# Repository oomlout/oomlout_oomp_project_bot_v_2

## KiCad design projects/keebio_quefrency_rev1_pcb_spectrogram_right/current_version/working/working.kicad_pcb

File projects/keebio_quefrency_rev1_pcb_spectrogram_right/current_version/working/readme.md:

# quefrency_rev1_pcb
 
## summary 
* id: keebio_quefrency_rev1_pcb_spectrogram_right
* user: keebio
* name: quefrency_rev1_pcb
* board: spectrogram_right
* repo: https://github.com/keebio/quefrency-rev1-pcb
* src_file_repo_kicad_pcb: spectrogram-right/spectrogram-right.kicad_pcb
* src_file_repo_kicad_pcb_link: https://github.com/keebio/quefrency-rev1-pcb/tree/main/spectrogram-right/spectrogram-right.kicad_pcb
* src_file_repo_kicad_sch: quefrency-right-65/quefrency-right-65.kicad_sch
* src_file_repo_kicad_sch_link: https://github.com/keebio/quefrency-rev1-pcb/tree/main/quefrency-right-65/quefrency-right-65.kicad_sch

* src_file_repo_sch: spectrogram-right/spectrogram-right.sch
* src_file_repo_sch_link: https://github.com/keebio/quefrency-rev1-pcb/tree/main/spectrogram-right/spectrogram-right.sch
* full details link: https://github.com/oomlout/oomlout_oomp_project_bot_v_2/tree/main/projects/keebio_quefrency_rev1_pcb_spectrogram_right/current_version/working

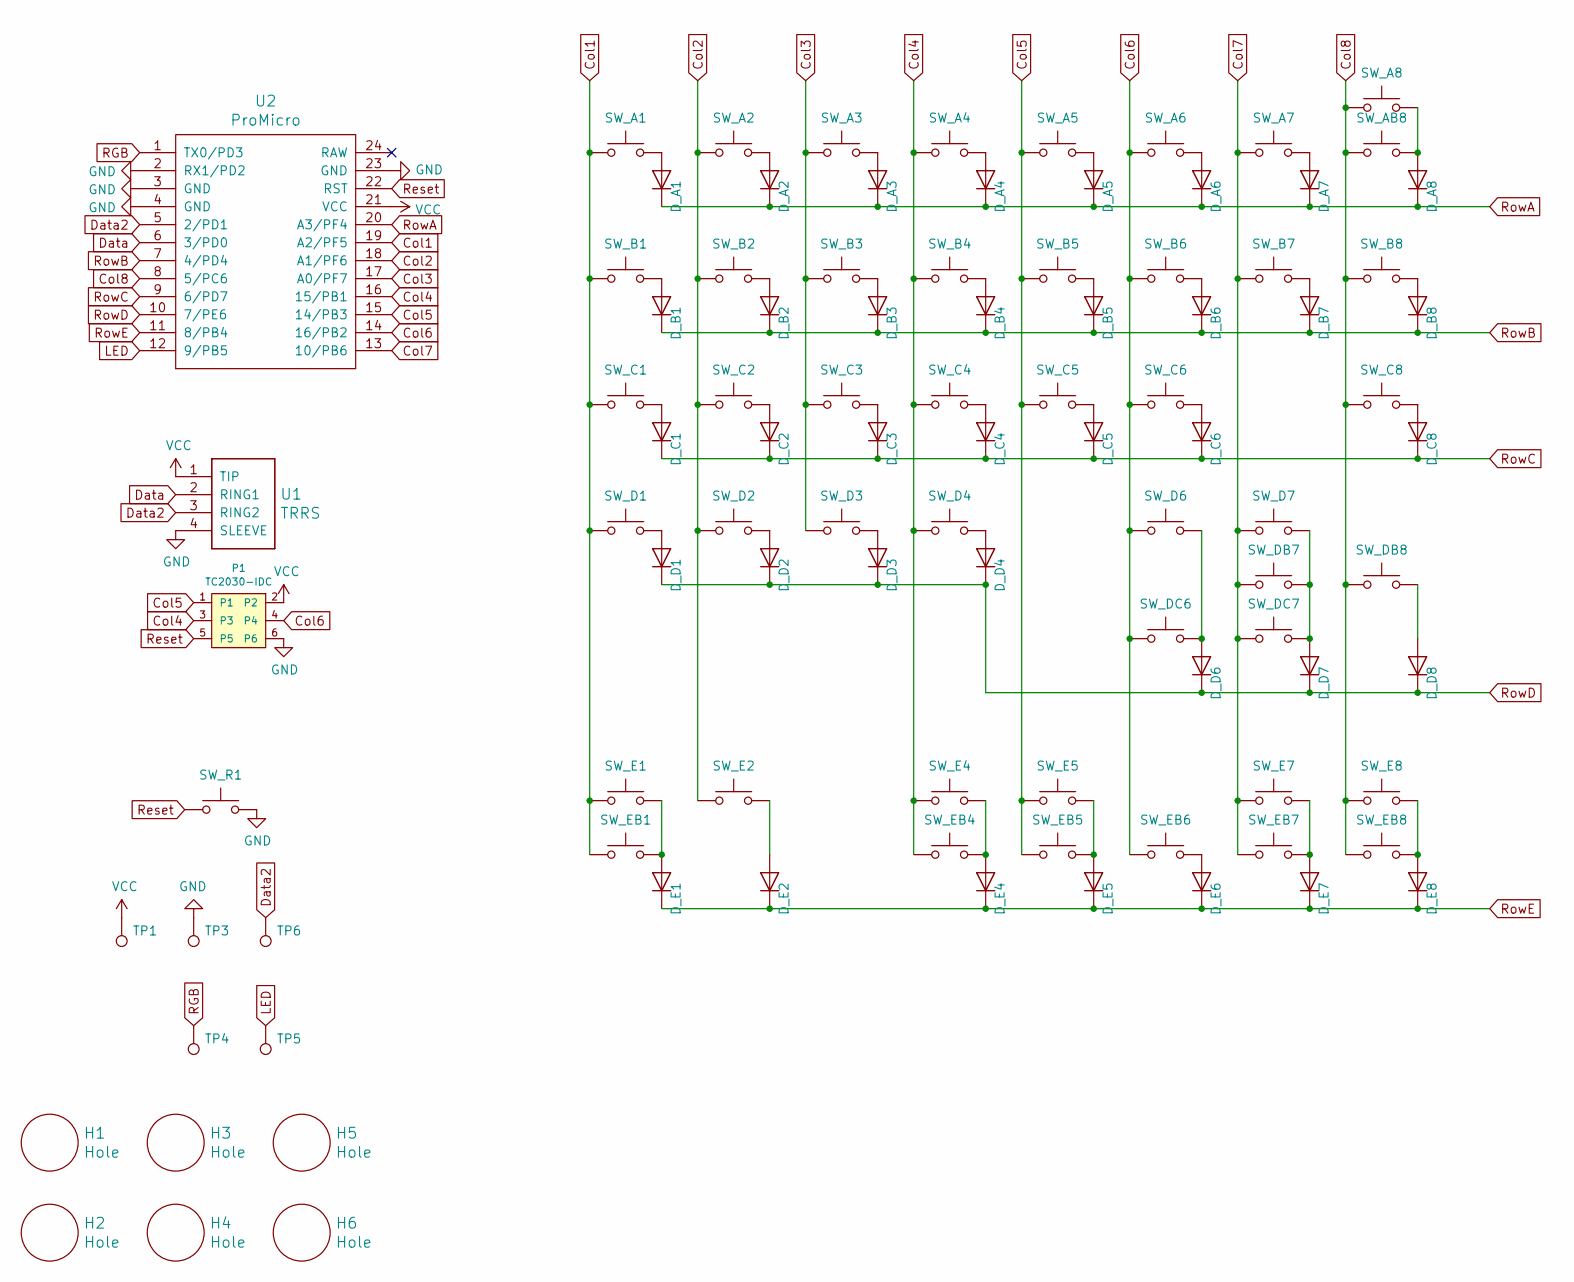
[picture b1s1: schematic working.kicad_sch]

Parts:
D_A1, D_A2, D_A3, D_A4, D_A5, D_A6, D_A7, D_A8: D; Diode-Hybrid-Back
D_B1, D_B2, D_B3, D_B4, D_B5, D_B6, D_B7, D_B8: D; Diode-Hybrid-Back
D_C1, D_C2, D_C3, D_C4, D_C5, D_C6, D_C8: D; Diode-Hybrid-Back
D_D1, D_D2, D_D3, D_D4, D_D6, D_D7, D_D8: D; Diode-Hybrid-Back
D_E1, D_E2, D_E4, D_E5, D_E6, D_E7, D_E8: D; Diode-Hybrid-Back
H1, H2, H3, H4, H5, H6: Hole; MountingHole_3.2mm_M3_ISO14580_Pad
P1: TC2030-IDC; TC2030-NL_SMALL
SW_A1, SW_A2, SW_A3, SW_A4, SW_A5, SW_A6, SW_A7: SW_Push; MX-1U-NoLED
SW_A8: SW_Push; MX-2U-ReversedStabilizers-NoLED
SW_AB8: SW_Push; MX-1U-NoLED
SW_B1, SW_B2, SW_B3, SW_B4, SW_B5, SW_B6, SW_B7: SW_Push; MX-1U-NoLED
SW_B8: SW_Push; MX-1.5U-NoLED
SW_C1, SW_C2, SW_C3, SW_C4, SW_C5, SW_C6: SW_Push; MX-1U-NoLED
SW_C8: SW_Push; MX-2.25U-NoLED
SW_D1, SW_D2, SW_D3, SW_D4, SW_D6: SW_Push; MX-1U-NoLED
SW_D7: SW_Push; MX-2.75U-NoLED
SW_DB7: SW_Push; MX-1.75U-NoLED
SW_DB8: SW_Push; MX-1U-NoLED
SW_DC6: SW_Push; MX-1.75U-NoLED
SW_DC7: SW_Push; MX-1U-NoLED
SW_E1: SW_Push; MX-2.75U-ReversedStabilizers-NoLED
SW_E2: SW_Push; MX-1.5U-NoLED
SW_E4, SW_E5, SW_E7, SW_E8: SW_Push; MX-1.25U-NoLED
SW_EB1: SW_Push; MX-1.25U-NoLED
SW_EB4, SW_EB5, SW_EB6, SW_EB7, SW_EB8: SW_Push; MX-1U-NoLED
SW_R1: Reset; SW_Tactile_SPST_Angled_MJTP1117
TP1: VCC; SinglePad
TP3: GND; SinglePad
TP4: RGB; SinglePad
TP5: LED; SinglePad
TP6: Extra Data; SinglePad
U1: TRRS; TRRS-PJ-320A
U2: ProMicro; ArduinoProMicro-ZigZag

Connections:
Col1: SW_A1.1, SW_B1.1, SW_C1.1, SW_D1.1, SW_E1.1, SW_EB1.1, U2.19 (A2/PF5)
Col2: SW_A2.1, SW_B2.1, SW_C2.1, SW_D2.1, SW_E2.1, U2.18 (A1/PF6)
Col3: SW_A3.1, SW_B3.1, SW_C3.1, SW_D3.1, U2.17 (A0/PF7)
Col4: P1.3, SW_A4.1, SW_B4.1, SW_C4.1, SW_D4.1, SW_E4.1, SW_EB4.1, U2.16 (15/PB1)
Col5: P1.1, SW_A5.1, SW_B5.1, SW_C5.1, SW_E5.1, SW_EB5.2, U2.15 (14/PB3)
Col6: P1.4, SW_A6.1, SW_B6.1, SW_C6.1, SW_D6.1, SW_DC6.2, SW_EB6.1, U2.14 (16/PB2)
Col7: SW_A7.1, SW_B7.1, SW_D7.2, SW_DB7.1, SW_DC7.2, SW_E7.1, SW_EB7.2, U2.13 (10/PB6)
Col8: SW_A8.1, SW_AB8.1, SW_B8.1, SW_C8.1, SW_DB8.1, SW_E8.1, SW_EB8.1, U2.8 (5/PC6)
Data: U1.2 (RING1), U2.6 (3/PD0)
Data2: TP6.1, U1.3 (RING2), U2.5 (2/PD1)
GND: P1.6, SW_R1.2, TP3.1, U1.4 (SLEEVE), U2.2 (RX1/PD2), U2.3 (GND), U2.4 (GND), U2.23 (GND)
LED: TP5.1, U2.12 (9/PB5)
unnamed: D_A1.2 (A), SW_A1.2
unnamed: D_A2.2 (A), SW_A2.2
unnamed: D_A3.2 (A), SW_A3.2
unnamed: D_A4.2 (A), SW_A4.2
unnamed: D_A5.2 (A), SW_A5.2
unnamed: D_A6.2 (A), SW_A6.2
unnamed: D_A7.2 (A), SW_A7.2
unnamed: D_A8.2 (A), SW_A8.2, SW_AB8.2
unnamed: D_B1.2 (A), SW_B1.2
unnamed: D_B2.2 (A), SW_B2.2
unnamed: D_B3.2 (A), SW_B3.2
unnamed: D_B4.2 (A), SW_B4.2
unnamed: D_B5.2 (A), SW_B5.2
unnamed: D_B6.2 (A), SW_B6.2
unnamed: D_B7.2 (A), SW_B7.2
unnamed: D_B8.2 (A), SW_B8.2
unnamed: D_C1.2 (A), SW_C1.2
unnamed: D_C2.2 (A), SW_C2.2
unnamed: D_C3.2 (A), SW_C3.2
unnamed: D_C4.2 (A), SW_C4.2
unnamed: D_C5.2 (A), SW_C5.2
unnamed: D_C6.2 (A), SW_C6.2
unnamed: D_C8.2 (A), SW_C8.2
unnamed: D_D1.2 (A), SW_D1.2
unnamed: D_D2.2 (A), SW_D2.2
unnamed: D_D3.2 (A), SW_D3.2
unnamed: D_D4.2 (A), SW_D4.2
unnamed: D_D6.2 (A), SW_D6.2, SW_DC6.1
unnamed: D_D7.2 (A), SW_D7.1, SW_DB7.2, SW_DC7.1
unnamed: D_D8.2 (A), SW_DB8.2
unnamed: D_E1.2 (A), SW_E1.2, SW_EB1.2
unnamed: D_E2.2 (A), SW_E2.2
unnamed: D_E4.2 (A), SW_E4.2, SW_EB4.2
unnamed: D_E5.2 (A), SW_E5.2, SW_EB5.1
unnamed: D_E6.2 (A), SW_EB6.2
unnamed: D_E7.2 (A), SW_E7.2, SW_EB7.1
unnamed: D_E8.2 (A), SW_E8.2, SW_EB8.2
RGB: TP4.1, U2.1 (TX0/PD3)
Reset: P1.5, SW_R1.1, U2.22 (RST)
RowA: D_A1.1 (K), D_A2.1 (K), D_A3.1 (K), D_A4.1 (K), D_A5.1 (K), D_A6.1 (K), D_A7.1 (K), D_A8.1 (K), U2.20 (A3/PF4)
RowB: D_B1.1 (K), D_B2.1 (K), D_B3.1 (K), D_B4.1 (K), D_B5.1 (K), D_B6.1 (K), D_B7.1 (K), D_B8.1 (K), U2.7 (4/PD4)
RowC: D_C1.1 (K), D_C2.1 (K), D_C3.1 (K), D_C4.1 (K), D_C5.1 (K), D_C6.1 (K), D_C8.1 (K), U2.9 (6/PD7)
RowD: D_D1.1 (K), D_D2.1 (K), D_D3.1 (K), D_D4.1 (K), D_D6.1 (K), D_D7.1 (K), D_D8.1 (K), U2.10 (7/PE6)
RowE: D_E1.1 (K), D_E2.1 (K), D_E4.1 (K), D_E5.1 (K), D_E6.1 (K), D_E7.1 (K), D_E8.1 (K), U2.11 (8/PB4)
VCC: P1.2, TP1.1, U1.1 (TIP), U2.21 (VCC)

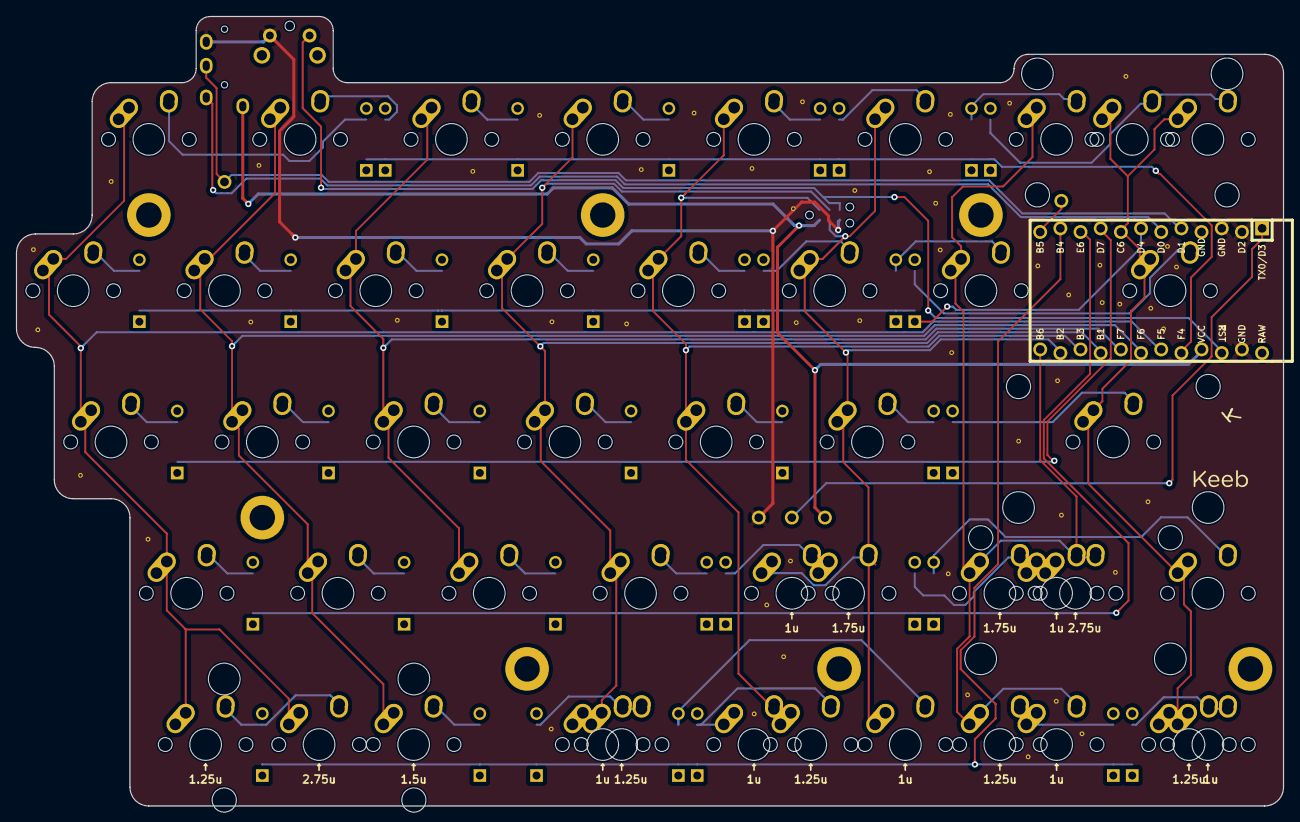
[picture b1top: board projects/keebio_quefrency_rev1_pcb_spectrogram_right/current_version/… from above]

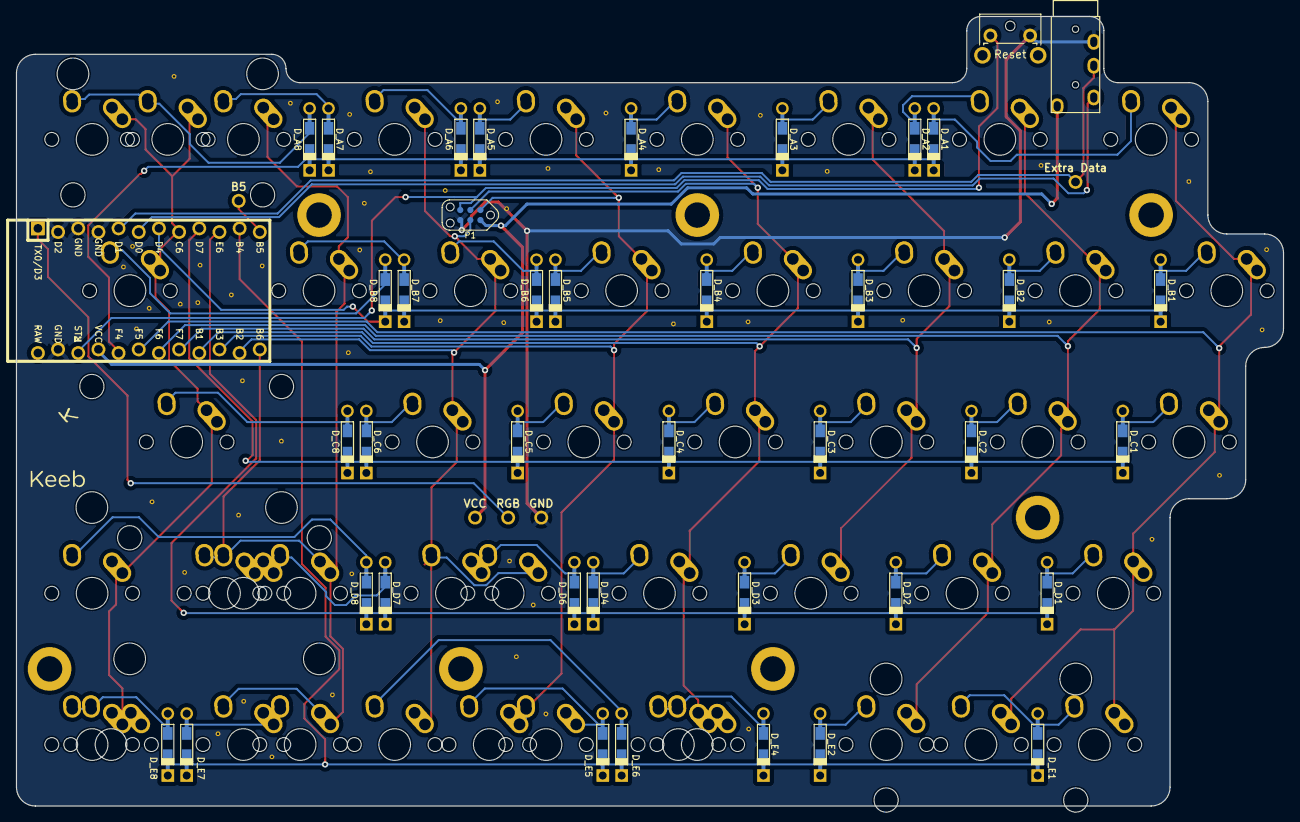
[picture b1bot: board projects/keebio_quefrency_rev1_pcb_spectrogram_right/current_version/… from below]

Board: 2 copper layers, 159.5 x 99.4 mm, 99 parts (8 on the bottom side), 57 nets.

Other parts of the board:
H6#2: Hole; MountingHole_3.2mm_M3_ISO14580_Pad

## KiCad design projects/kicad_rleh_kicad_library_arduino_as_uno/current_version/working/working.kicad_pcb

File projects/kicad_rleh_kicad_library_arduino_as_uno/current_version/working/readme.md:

# kicad_library
 
## summary 
* id: kicad_rleh_kicad_library_arduino_as_uno
* user: kicad_rleh
* name: kicad_library
* board: arduino_as_uno
* repo: https://github.com/kicad-rleh/kicad-library
* src_file_repo_kicad_pcb: template/Arduino_As_Uno_R3/Arduino_As_Uno.kicad_pcb
* src_file_repo_kicad_pcb_link: https://github.com/kicad-rleh/kicad-library/tree/master/template/Arduino_As_Uno_R3/Arduino_As_Uno.kicad_pcb

* src_file_repo_sch: template/Arduino_As_Uno_R3/Arduino_As_Uno.sch
* src_file_repo_sch_link: https://github.com/kicad-rleh/kicad-library/tree/master/template/Arduino_As_Uno_R3/Arduino_As_Uno.sch
* full details link: https://github.com/oomlout/oomlout_oomp_project_bot_v_2/tree/main/projects/kicad_rleh_kicad_library_arduino_as_uno/current_version/working

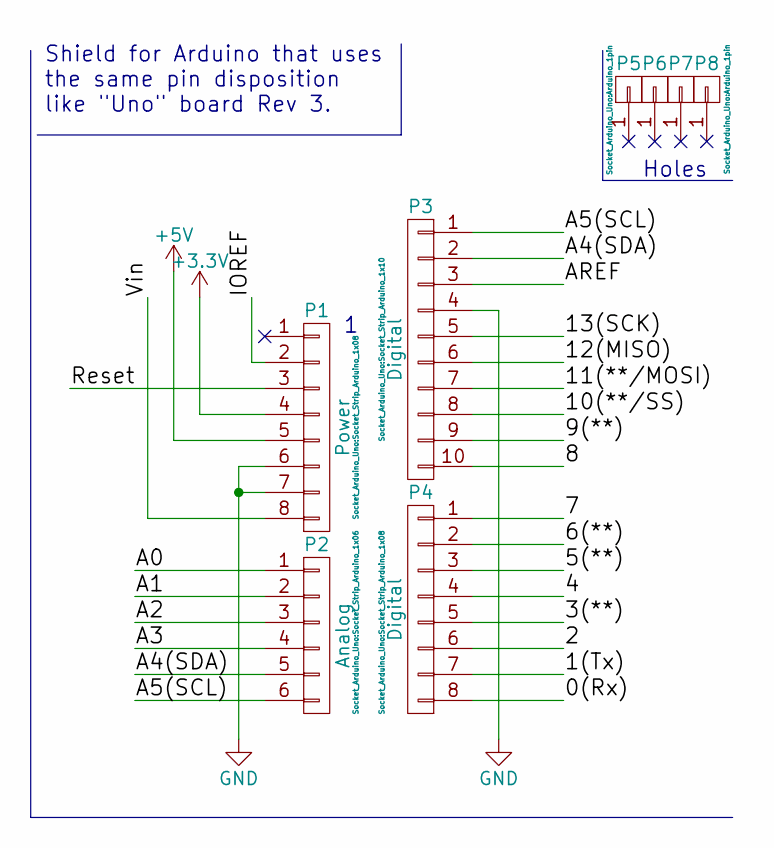
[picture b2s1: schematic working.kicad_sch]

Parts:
P1: Power; Socket_Strip_Arduino_1x08
P2: Analog; Socket_Strip_Arduino_1x06
P3: Digital; Socket_Strip_Arduino_1x10
P4: Digital; Socket_Strip_Arduino_1x08
P5, P6, P7, P8: CONN_01X01; Arduino_1pin

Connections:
+3V3: P1.4
+5V: P1.5
/0(Rx): P4.8
/1(Tx): P4.7
/2: P4.6
/3(**): P4.5
/4: P4.4
/5(**): P4.3
/6(**): P4.2
/7: P4.1
/8: P3.10
/9(**): P3.9
/10(**/SS): P3.8
/11(**/MOSI): P3.7
/12(MISO): P3.6
/13(SCK): P3.5
/A0: P2.1
/A1: P2.2
/A2: P2.3
/A3: P2.4
/A4(SDA): P2.5, P3.2
/A5(SCL): P2.6, P3.1
/AREF: P3.3
/IOREF: P1.2
/Reset: P1.3
/Vin: P1.8
GND: P1.6, P1.7, P3.4

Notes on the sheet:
Holes
Shield for Arduino that uses the same pin disposition like "Uno" board Rev 3.

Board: 2 copper layers, 8 parts (0 on the bottom side), 3 nets, no tracks yet.

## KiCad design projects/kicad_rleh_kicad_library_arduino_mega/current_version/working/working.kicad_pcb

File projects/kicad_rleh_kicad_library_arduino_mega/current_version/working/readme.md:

# kicad_library
 
## summary 
* id: kicad_rleh_kicad_library_arduino_mega
* user: kicad_rleh
* name: kicad_library
* board: arduino_mega
* repo: https://github.com/kicad-rleh/kicad-library
* src_file_repo_kicad_pcb: template/Arduino_Mega_R3/Arduino_Mega.kicad_pcb
* src_file_repo_kicad_pcb_link: https://github.com/kicad-rleh/kicad-library/tree/master/template/Arduino_Mega_R3/Arduino_Mega.kicad_pcb

* src_file_repo_sch: template/Arduino_Mega_R3/Arduino_Mega.sch
* src_file_repo_sch_link: https://github.com/kicad-rleh/kicad-library/tree/master/template/Arduino_Mega_R3/Arduino_Mega.sch
* full details link: https://github.com/oomlout/oomlout_oomp_project_bot_v_2/tree/main/projects/kicad_rleh_kicad_library_arduino_mega/current_version/working

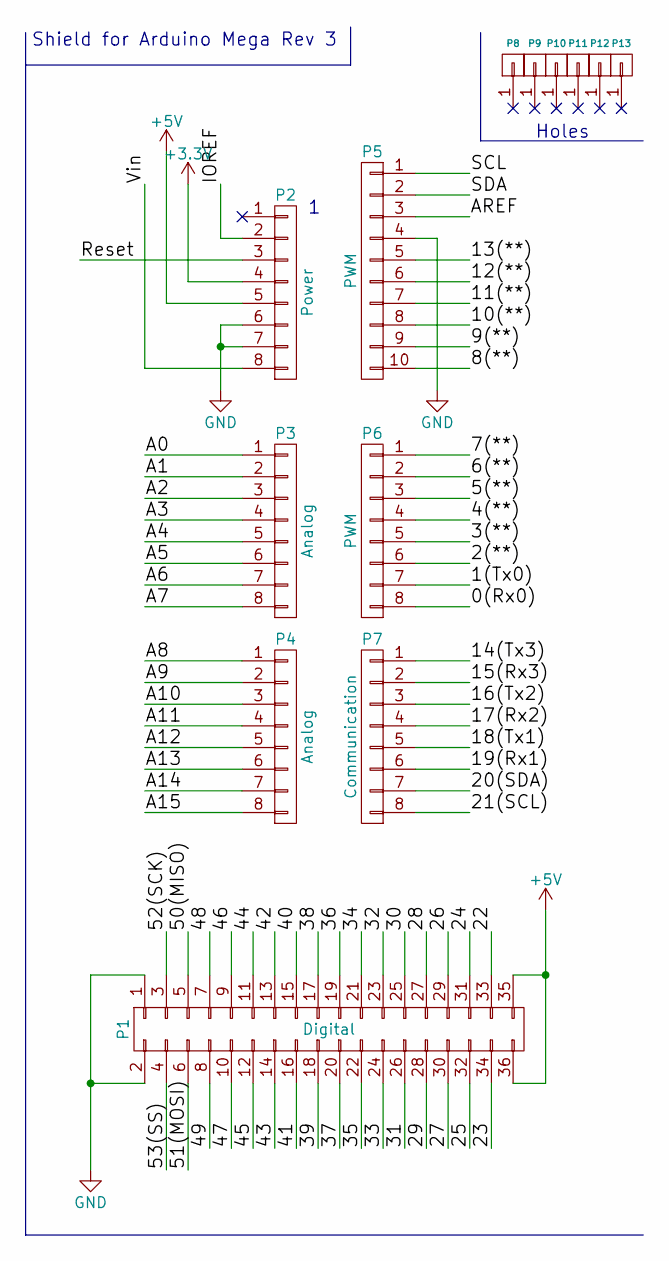
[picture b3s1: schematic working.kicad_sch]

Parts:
P1: Digital; Socket_Strip_Arduino_2x18
P2: Power; Socket_Strip_Arduino_1x08
P3, P4: Analog; Socket_Strip_Arduino_1x08
P5: PWM; Socket_Strip_Arduino_1x10
P6: PWM; Socket_Strip_Arduino_1x08
P7: Communication; Socket_Strip_Arduino_1x08
P8, P9, P10, P11, P12, P13: CONN_01X01; Arduino_1pin

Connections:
+3V3: P2.4
+5V: P1.35, P1.36, P2.5
/0(Rx0): P6.8
/1(Tx0): P6.7
/2(**): P6.6
/3(**): P6.5
/4(**): P6.4
/5(**): P6.3
/6(**): P6.2
/7(**): P6.1
/8(**): P5.10
/9(**): P5.9
/10(**): P5.8
/11(**): P5.7
/12(**): P5.6
/13(**): P5.5
/14(Tx3): P7.1
/15(Rx3): P7.2
/16(Tx2): P7.3
/17(Rx2): P7.4
/18(Tx1): P7.5
/19(Rx1): P7.6
/20(SDA): P7.7
/21(SCL): P7.8
/22: P1.33
/23: P1.34
/24: P1.31
/25: P1.32
/26: P1.29
/27: P1.30
/28: P1.27
/29: P1.28
/30: P1.25
/31: P1.26
/32: P1.23
/33: P1.24
/34: P1.21
/35: P1.22
/36: P1.19
/37: P1.20
/38: P1.17
/39: P1.18
/40: P1.15
/41: P1.16
/42: P1.13
/43: P1.14
/44: P1.11
/45: P1.12
/46: P1.9
/47: P1.10
/48: P1.7
/49: P1.8
/50(MISO): P1.5
/51(MOSI): P1.6
/52(SCK): P1.3
/53(SS): P1.4
/A0: P3.1
/A1: P3.2
/A2: P3.3
/A3: P3.4
/A4: P3.5
/A5: P3.6
/A6: P3.7
/A7: P3.8
/A8: P4.1
/A9: P4.2
/A10: P4.3
/A11: P4.4
/A12: P4.5
/A13: P4.6
/A14: P4.7
/A15: P4.8
/AREF: P5.3
/IOREF: P2.2
/Reset: P2.3
/SCL: P5.1
/SDA: P5.2
/Vin: P2.8
GND: P1.1, P1.2, P2.6, P2.7, P5.4

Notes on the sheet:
Shield for Arduino Mega Rev 3
Holes

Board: 2 copper layers, 13 parts (0 on the bottom side), 2 nets, no tracks yet.

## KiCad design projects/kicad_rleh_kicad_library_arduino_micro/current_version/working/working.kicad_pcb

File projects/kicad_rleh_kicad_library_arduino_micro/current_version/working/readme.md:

# kicad_library
 
## summary 
* id: kicad_rleh_kicad_library_arduino_micro
* user: kicad_rleh
* name: kicad_library
* board: arduino_micro
* repo: https://github.com/kicad-rleh/kicad-library
* src_file_repo_kicad_pcb: template/Arduino_Micro/Arduino_Micro.kicad_pcb
* src_file_repo_kicad_pcb_link: https://github.com/kicad-rleh/kicad-library/tree/master/template/Arduino_Micro/Arduino_Micro.kicad_pcb

* src_file_repo_sch: template/Arduino_Micro/Arduino_Micro.sch
* src_file_repo_sch_link: https://github.com/kicad-rleh/kicad-library/tree/master/template/Arduino_Micro/Arduino_Micro.sch
* full details link: https://github.com/oomlout/oomlout_oomp_project_bot_v_2/tree/main/projects/kicad_rleh_kicad_library_arduino_micro/current_version/working

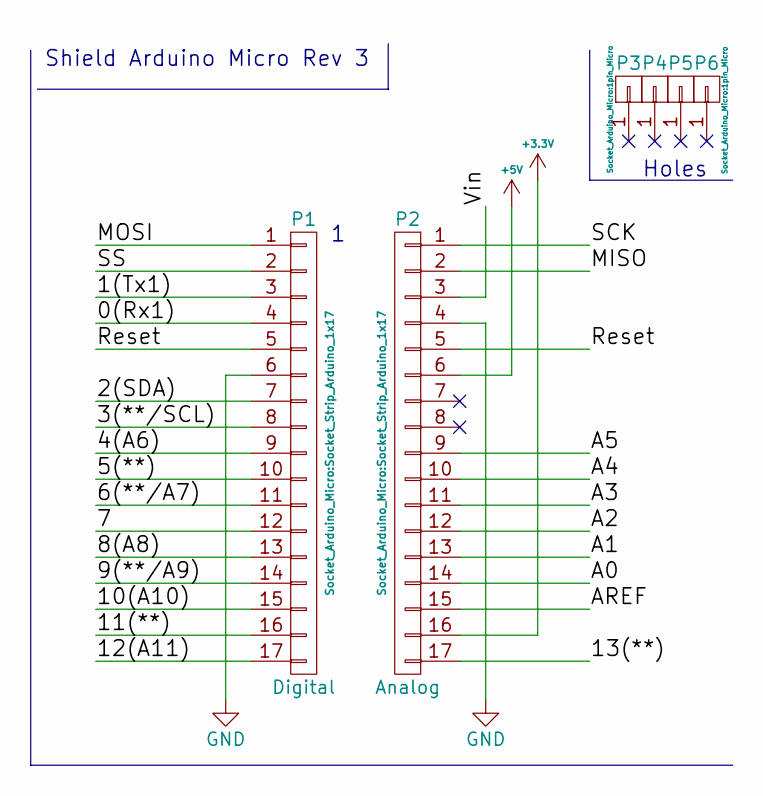
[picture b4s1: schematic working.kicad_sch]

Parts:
P1: Digital; Socket_Strip_Arduino_1x17
P2: Analog; Socket_Strip_Arduino_1x17
P3, P4, P5, P6: CONN_01X01; 1pin_Micro

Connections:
+3V3: P2.16
+5V: P2.6
/0(Rx1): P1.4
/1(Tx1): P1.3
/2(SDA): P1.7
/3(**/SCL): P1.8
/4(A6): P1.9
/5(**): P1.10
/6(**/A7): P1.11
/7: P1.12
/8(A8): P1.13
/9(**/A9): P1.14
/10(A10): P1.15
/11(**): P1.16
/12(A11): P1.17
/13(**): P2.17
/A0: P2.14
/A1: P2.13
/A2: P2.12
/A3: P2.11
/A4: P2.10
/A5: P2.9
/AREF: P2.15
/MISO: P2.2
/MOSI: P1.1
/Reset: P1.5, P2.5
/SCK: P2.1
/SS: P1.2
/Vin: P2.3
GND: P1.6, P2.4

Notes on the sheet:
Shield Arduino Micro Rev 3
Holes

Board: 2 copper layers, 6 parts (0 on the bottom side), 2 nets, no tracks yet.
